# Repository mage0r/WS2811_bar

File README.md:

WS2811_bar
=============

This project drives a LED bar graph using a single pin from your microcontroller.

It is designed around using the popular WS2811 LED driver chip commonly used in the adafruit neopixels.  This also means several bar graphs can be chained together or the bar graph can follow a sequence of WS2811 or WS2812 LED's.

There has three sections, a kicad circuit diagram, an arduino sketch using the neopixel library from adafruit and lastly a few photos of it in action.

Of course, this is a hacky way to use these chips and there are several disadvantages.  Chifely, each chip drives 3 seperate LED's, meaning if you want to iterate through them activating each one, you have to iterate not only through the "pixels" but also through the "colours".

Also, as each chip drives 3 LED's and there are 10 LED's all up, there are two channels "spare", these are the last two of the last pixel.

Depending on the WS2811 chip you use, you may end up with a GRB rather than a RGB.  Just because there wasn't enough confusion already...

Improvements and changes cheerfully accepted.

(https://www.youtube.com/watch?v=YOKhcFke9yQ)

CREDITS
------------
This board was designed by John Spencer - john.spencer.9000@gmail.com - https://github.com/mage0r

SPECIAL THANKS
------------
To the creators and maintainers of the KiCAD open-source EDA suite.
To the HackMelbourne (CCHS, http://hackmelbourne.org) community of Melbourne, Australia. Especially Lachlan Maher, and Bob Powers.
To all other open-source developers whose countless hours supported every other aspect of this design.
Extra thanks to Bob because I copied his README.md almost verbatim...

DISTRIBUTION
------------
The specific terms of distribution of this project are governed by the
license referenced below. Please contact the copyright owner if you wish to modify the board for distribution. Please utilize this design for personal or research projects. Please acknowledge all contributors.

LICENSE
-------
Licensed under the TAPR Open Hardware License (www.tapr.org/OHL).
The "license" sub-folder also contains a copy of this license in plain text format.

Copyright John Spencer 2013
john.spencer.9000@gmail.com

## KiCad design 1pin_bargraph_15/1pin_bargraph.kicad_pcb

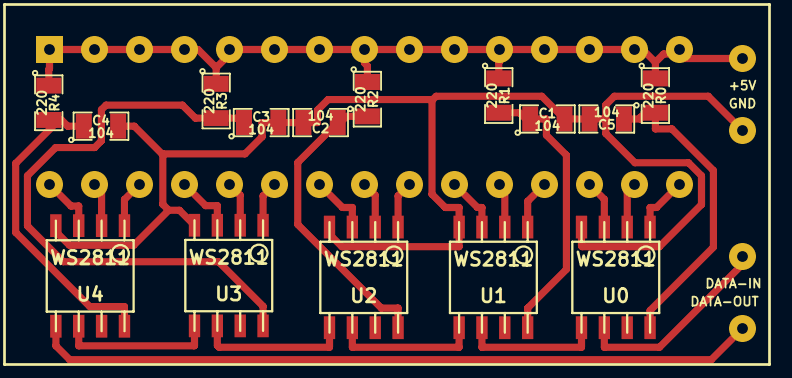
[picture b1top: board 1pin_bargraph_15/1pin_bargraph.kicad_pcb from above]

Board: 2 copper layers, 16 parts (0 on the bottom side), 28 nets.

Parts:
BAR1: DOT-BAR15; 15_PIN_BAR
C1, C2, C3, C4, C5: 104; SM0805
R0, R1, R2, R3, R4: 220; SM0805
U0, U1, U2, U3, U4: WS2811; so-8

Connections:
+5V: BAR1.1, BAR1.2, BAR1.3, BAR1.4, BAR1.5, BAR1.6, BAR1.7, BAR1.8, BAR1.9, BAR1.10, BAR1.11, BAR1.12, BAR1.13, BAR1.14, BAR1.15, BAR1.31, R0.1, R1.1, R2.1, R3.1, R4.1
GND: BAR1.32, C1.2, C2.2, C3.2, C4.2, C5.2, U0.4, U1.4, U2.4, U3.4, U4.4
unnamed: BAR1.21, U1.3
unnamed: BAR1.20, U1.2
unnamed: BAR1.29, U4.2
unnamed: BAR1.26, U3.2
unnamed: BAR1.23, U2.2
unnamed: BAR1.28, U4.1
unnamed: U2.5, U3.6
unnamed: C3.1, R3.2, U3.8
unnamed: C4.1, R4.2, U4.8
unnamed: U3.5, U4.6
unnamed: BAR1.30, U4.3
unnamed: U1.5, U2.6
unnamed: U0.5, U1.6
unnamed: BAR1.33, U4.5
unnamed: BAR1.34, U0.6
unnamed: BAR1.18, U0.3
unnamed: BAR1.27, U3.3
unnamed: BAR1.17, U0.2
unnamed: BAR1.25, U3.1
unnamed: BAR1.24, U2.3
unnamed: BAR1.22, U2.1
unnamed: C1.1, R1.2, U1.8
unnamed: BAR1.16, U0.1
unnamed: C5.1, R0.2, U0.8
unnamed: C2.1, R2.2, U2.8
unnamed: BAR1.19, U1.1

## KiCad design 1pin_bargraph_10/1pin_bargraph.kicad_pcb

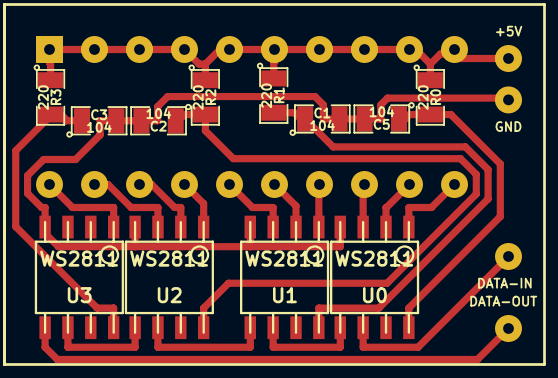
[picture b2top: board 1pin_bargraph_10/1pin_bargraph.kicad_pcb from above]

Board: 2 copper layers, 13 parts (0 on the bottom side), 21 nets.

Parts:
BAR1: DOT-BAR10-DATA; 10_PIN_BAR
C1, C2, C3, C5: 104; SM0805
R0, R1, R2, R3: 220; SM0805
U0, U1, U2, U3: WS2811; so-8

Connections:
+5V: BAR1.1, BAR1.2, BAR1.3, BAR1.4, BAR1.5, BAR1.6, BAR1.7, BAR1.8, BAR1.9, BAR1.10, BAR1.21, R0.1, R1.1, R2.1, R3.1
GND: BAR1.22, C1.2, C2.2, C3.2, C5.2, U0.4, U1.4, U2.4, U3.4
unnamed: C3.1, R3.2, U3.8
unnamed: U0.5, U1.6
unnamed: U1.5, U2.6
unnamed: U2.5, U3.6
unnamed: C2.1, R2.2, U2.8
unnamed: BAR1.23, U3.5
unnamed: BAR1.18, U2.2
unnamed: BAR1.24, U0.6
unnamed: BAR1.19, U2.3
unnamed: BAR1.17, U2.1
unnamed: BAR1.20, U3.1
unnamed: BAR1.14, U1.1
unnamed: BAR1.16, U1.3
unnamed: C1.1, R1.2, U1.8
unnamed: BAR1.11, U0.1
unnamed: BAR1.12, U0.2
unnamed: BAR1.13, U0.3
unnamed: C5.1, R0.2, U0.8
unnamed: BAR1.15, U1.2

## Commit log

2014-01-10 Initial Commit
    This is a big commit and includes everything except the library and code
    examples.
2014-01-10 added images to readme
    Image of the boards in the readme
2014-01-10 Close bracket for link
2014-01-10 and added a link to the hackmelbourne webpage
2014-01-11 Changes to project description
2014-01-23 Added test code
2014-02-25 updated test code
2014-02-25 Added Youtube link
2014-02-25 fixed link
